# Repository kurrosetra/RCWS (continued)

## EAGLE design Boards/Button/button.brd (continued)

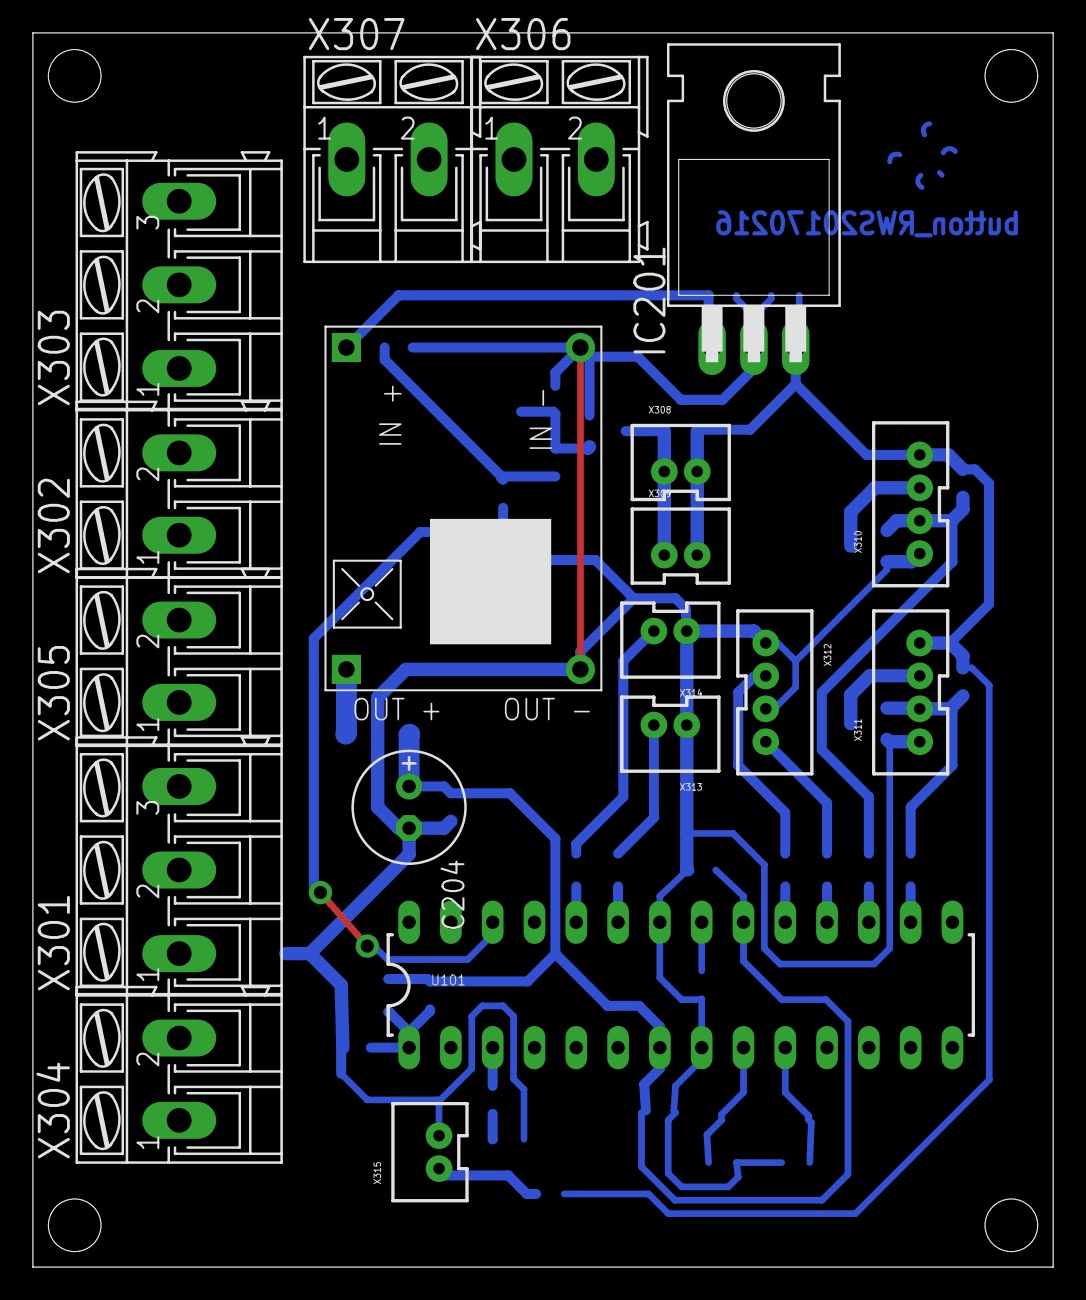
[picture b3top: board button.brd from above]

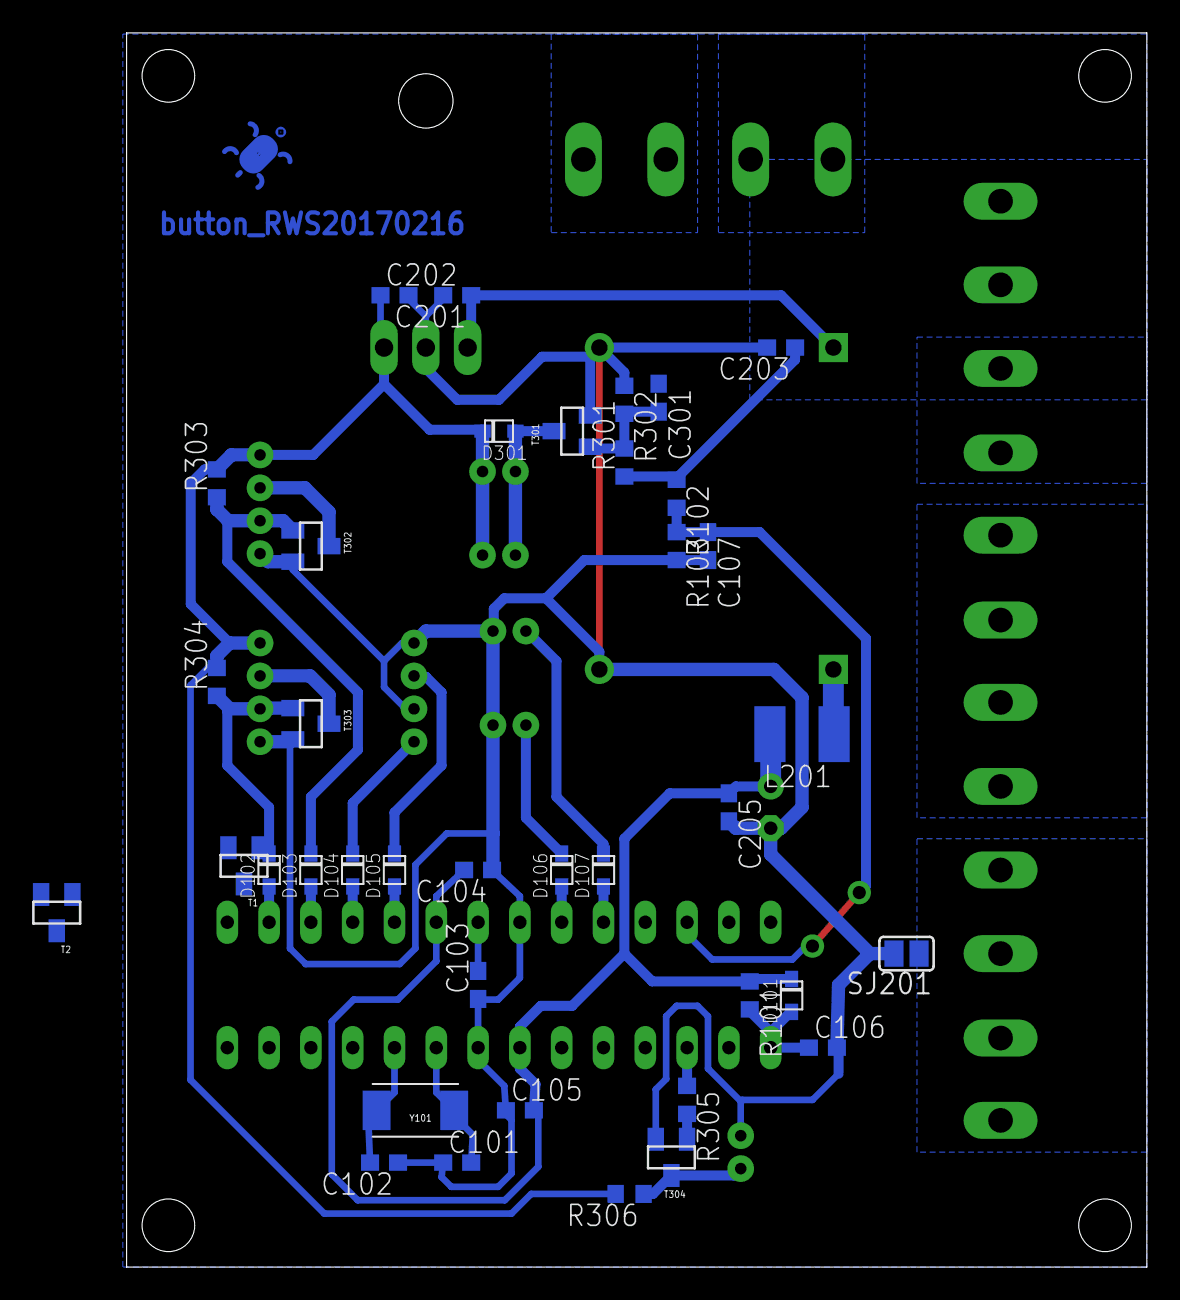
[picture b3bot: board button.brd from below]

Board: 2 copper layers, 62.0 x 75.0 mm, 58 parts (38 on the bottom side), 34 nets.

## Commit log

2018-02-23 add documentation
    - add canID
    - add wiring diagram
    - add wiring pinout
2018-02-23 add boards
2018-03-05 Initial firmware commit
    Commit:
    1. Button firmware
    2. Panel firmware
    3. modify ignore rule
2018-04-09 motorControl update
2018-04-10 update
    - motorControl update:
    > motorPan stop function update, but cant implement to motorTilt
    > when startup, motorTilt seem doesnt response to command
    - add optronik firmware initial commit, based on FCS's optronik firmware
2018-04-11 firmware & doc update
    - joystick data update
    - add trigger function
    - update optronik firmware
2018-04-12 Update
    - add GY-80 IMU
2018-04-23 Revert "Update"
    This reverts commit fe09edef820f781b01c554e8742a3b63bd834693.
2018-04-23 add extBoard & update panel & motorControl board
    > update panel board
    > update motorControl board
    >add extBoard:
    - to replace mouse movement & left/right click
    - add clear target button
    - add manual lrf value manually using keypad and display it on 4 digits 7-segment
2018-04-24 update extBoard
    Completed extBoard firmware
2018-04-27 20180427 update
    Wiring:
    - update wiring diagram
    Optronik:
    - add IMU option (vectornav or custom IMU GY-80)
    Panel & MotorControl:
    - change "BUS_PANEL_x" to "BUS_MTR_CMD_x"
2018-04-27 20180427 update 2
    optronik:
    > all function ready
    Panel:
    > all function ready
    > need to find PID tuning for track movement & stab movement
2018-04-27 add extBoard connection in Panel.ino
2018-09-24 v1.0.0
    final release
